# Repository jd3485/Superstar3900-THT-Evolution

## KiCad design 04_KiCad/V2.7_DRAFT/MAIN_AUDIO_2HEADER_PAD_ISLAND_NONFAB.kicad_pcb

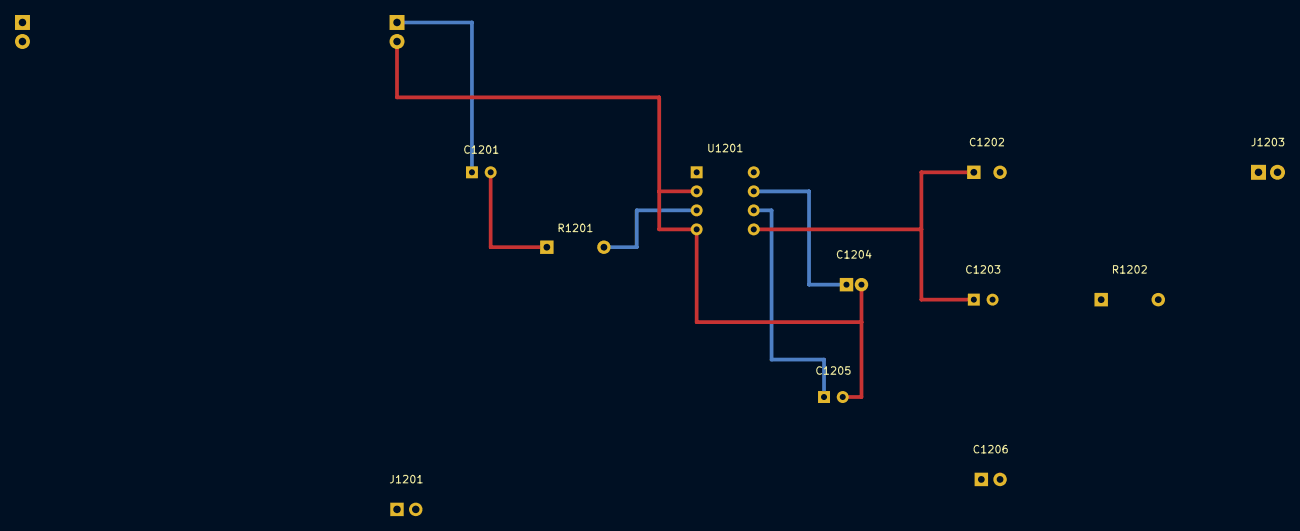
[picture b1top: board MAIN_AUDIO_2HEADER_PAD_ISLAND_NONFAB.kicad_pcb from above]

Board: 2 copper layers, 13 parts (0 on the bottom side), 9 nets.

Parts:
C1201: 100nF_50V_INPUT_UNQUALIFIED; C_Disc_D3.0mm_W1.6mm_P2.50mm
C1202: 220uF_16V_POS_TO_AMP_OUT_CANDIDATE_NONFAB; CP_Radial_D8.0mm_P3.50mm
C1203: 47nF_50V_ZOBEL_CANDIDATE_NONFAB; C_Disc_D3.0mm_W1.6mm_P2.50mm
C1204: 10uF_16V_BYPASS_CANDIDATE; CP_Radial_D5.0mm_P2.00mm
C1205: 100nF_25V_DECOUPLE_CANDIDATE; C_Disc_D3.0mm_W1.6mm_P2.50mm
C1206: 100uF_16V_BULK_CANDIDATE_NONFAB; CP_Radial_D6.3mm_P2.50mm
J1201: BENCH_6V_SOURCE_UNQUALIFIED_CANDIDATE_NONFAB; JST_XH_B2B-XH-A_1x02_P2.50mm_Vertical
J1202, J1502: NONFAB_MAIN_AUDIO_HEADER_PAD_ISLAND; PinHeader_1x02_P2.54mm_Vertical
J1203: SPK_OUT_CANDIDATE_NONFAB; PinHeader_1x02_P2.54mm_Vertical
R1201: 10k_0p25W_INPUT_UNQUALIFIED; R_Axial_DIN0207_L6.3mm_D2.5mm_P7.62mm_Horizontal
R1202: 10R_0p25W_ZOBEL_CANDIDATE_NONFAB; R_Axial_DIN0207_L6.3mm_D2.5mm_P7.62mm_Horizontal
U1201: LM386N-1/NOPB_CANDIDATE; DIP-8_W7.62mm

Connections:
AMP_IN: R1201.2, U1201.3
AMP_OUT: C1202.1, C1203.1, U1201.5
AUDIO_6V_LAB: C1205.1, C1206.1, J1201.1, U1201.6
AUDIO_IN: C1201.1, J1202.1
BYPASS: C1204.1, U1201.7
GND: C1204.2, C1205.2, C1206.2, J1201.2, J1202.2, J1203.2, R1202.2, U1201.2, U1201.4
PRE_IN: C1201.2, R1201.1
SPK_HOT: C1202.2, J1203.1
ZOBEL: C1203.2, R1202.1

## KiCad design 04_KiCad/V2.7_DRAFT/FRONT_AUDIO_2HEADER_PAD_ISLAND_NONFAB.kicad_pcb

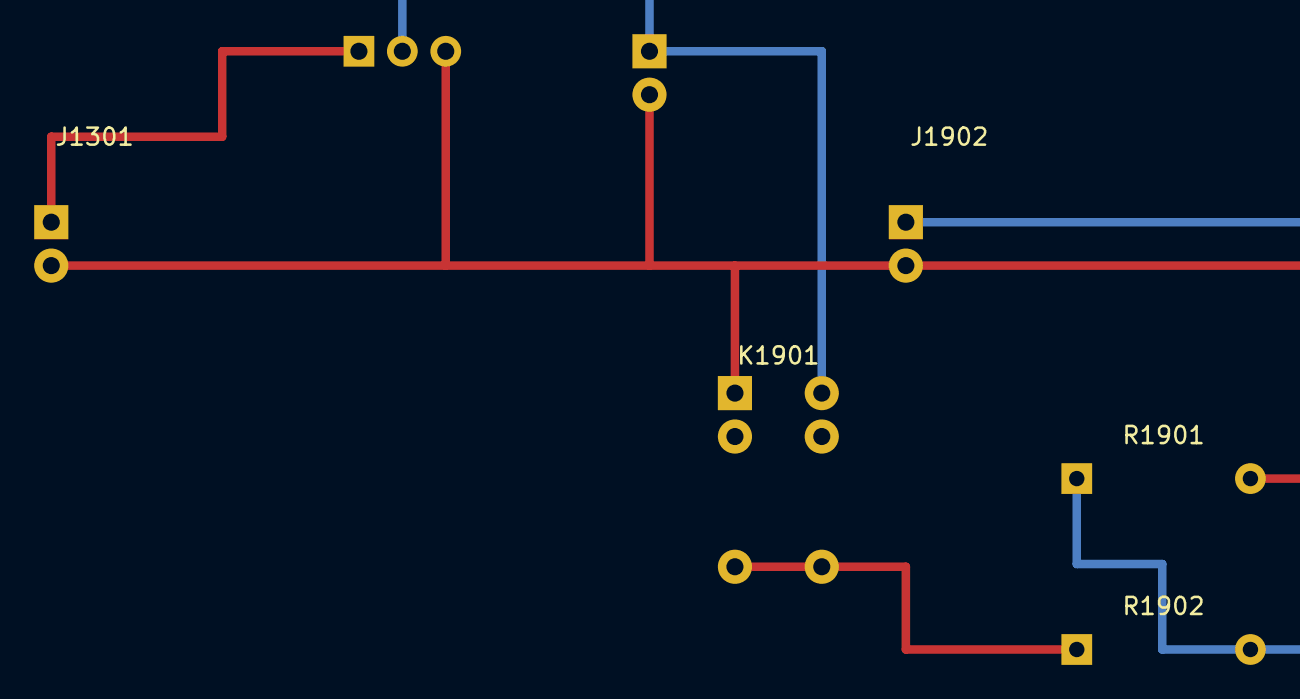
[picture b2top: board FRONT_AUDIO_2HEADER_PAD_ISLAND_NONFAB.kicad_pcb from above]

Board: 2 copper layers, 7 parts (0 on the bottom side), 5 nets.

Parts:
J1301, J1902: NONFAB_FRONT_AUDIO_HEADER_PAD_ISLAND; PinHeader_1x02_P2.54mm_Vertical
J1302: NONFAB_VOLUME_WIPER_HEADER; PinHeader_1x02_P2.54mm_Vertical
K1901: G5V1_DC5_SIXPIN_UNQUALIFIED; G5V-1_DC5_OEM_6PIN_CANDIDATE
R1901: 100k bleed, provisional; R_Axial_DIN0207_L6.3mm_D2.5mm_P10.16mm_Horizontal
R1902: 1k series, provisional; R_Axial_DIN0207_L6.3mm_D2.5mm_P10.16mm_Horizontal
RV1301: NONFAB_VOLUME_THT_CANDIDATE; Potentiometer_THT_3Pin_PROVISIONAL

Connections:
AF_GND: J1301.2, J1302.2, J1902.2, K1901.1, R1901.2, RV1301.3
AMP_INPUT_MUTED: J1902.1, R1901.1, R1902.2
DEMOD_AUDIO: J1301.1, RV1301.1
RELAY_COM_AUDIO: K1901.5, K1901.6, R1902.1
VOL_WIPER_TO_AMP: J1302.1, K1901.10, RV1301.2

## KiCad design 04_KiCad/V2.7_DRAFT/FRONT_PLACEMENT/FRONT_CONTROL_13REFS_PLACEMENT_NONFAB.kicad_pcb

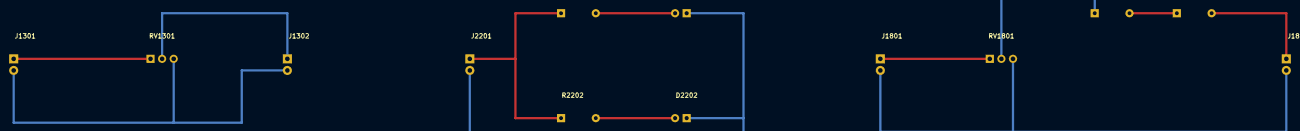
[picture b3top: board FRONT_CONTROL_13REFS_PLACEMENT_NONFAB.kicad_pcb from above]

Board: 2 copper layers, 13 parts (0 on the bottom side), 12 nets.

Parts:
D2201, D2202: NONFAB_LED_THT_PLACEMENT_ONLY; LED_D5.0mm
J1301, J1302, J1801, J1802, J2201: NONFAB_HEADER_THT_PLACEMENT_ONLY; PinHeader_1x02_P2.54mm_Vertical
R1801, R1802, R2201, R2202: NONFAB_RES_THT_PLACEMENT_ONLY; R_Axial_DIN0207_L6.3mm_D2.5mm_P7.62mm_Horizontal
RV1301, RV1801: NONFAB_POT_THT_PLACEMENT_ONLY; Potentiometer_THT_3Pin_PROVISIONAL

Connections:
AF_GND: J1301.2, J1302.2, RV1301.3
DEMOD_AUDIO: J1301.1, RV1301.1
ILLUM_5V_LAB: J2201.1, R2201.1, R2202.1
ILLUM_LED1_A: D2201.2, R2201.2
ILLUM_LED2_A: D2202.2, R2202.2
ILLUM_RETURN_LAB: D2201.1, D2202.1, J2201.2
METER_DRIVE_CANDIDATE: J1801.1, RV1801.1
METER_LIMIT_STAGE1: R1801.2, R1802.1
METER_POS_LIMITED: J1802.1, R1802.2
METER_RETURN: J1801.2, J1802.2, RV1801.3
METER_TRIM_OUTPUT: R1801.1, RV1801.2
VOL_WIPER_TO_AMP: J1302.1, RV1301.2

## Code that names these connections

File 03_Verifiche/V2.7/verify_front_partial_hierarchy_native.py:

#!/usr/bin/env python3
"""KiCad9 hierarchical FRONT integration pilot, five real THT sheets with four explicit inter-sheet nets.

Intended future FRONT parent but NOT an approved product schematic: existing
volume, LED, S-meter, relay contact and dual NPN coil driver sheets are included without making power,
return, cable or S-meter driver electrical interconnections. Fail on ERC violations
and accidental net merging across child pages.
"""
from pathlib import Path
import re
import subprocess
import tempfile

ROOT=Path(__file__).resolve().parents[2]
SCH=ROOT/"04_KiCad/V2.7_DRAFT/FRONT_CONTROL_PARTIAL_V2_7_DRAFT.kicad_sch"
CHILDREN=(
    ROOT/"04_KiCad/V2.7_DRAFT/FRONT_VOLUME/FRONT_VOLUME_THT_V2_7_DRAFT.kicad_sch",
    ROOT/"04_KiCad/V2.7_DRAFT/FRONT_ILLUM_BENCH/FRONT_ILLUM_BENCH_V2_7_DRAFT.kicad_sch",
    ROOT/"04_KiCad/V2.7_DRAFT/FRONT_SMETER/FRONT_SMETER_THT_V2_7_DRAFT.kicad_sch",
    ROOT/"04_KiCad/V2.7_DRAFT/FRONT_MUTE_NC_RELAY/FRONT_NC_MUTE_CONTACT_THT_V2_7_DRAFT.kicad_sch",
    ROOT/"04_KiCad/V2.7_DRAFT/FRONT_MUTE_COIL_DRIVER/FRONT_NC_MUTE_DUAL_ENABLE_COIL_DRIVER_V2_7_DRAFT.kicad_sch",
)
PARTITIONS={
    "DEMOD_AUDIO":{("J1301","1"),("RV1301","1")},
    "AF_GND":{("J1301","2"),("RV1301","3"),("J1302","2")},
    "VOL_WIPER_TO_AMP":{("RV1301","2"),("J1302","1")},
    "ILLUM_5V_LAB":{("J2201","1"),("R2201","1"),("R2202","1")},
    "ILLUM_RETURN_LAB":{("J2201","2"),("D2201","1"),("D2202","1")},
    "ILLUM_LED1_A":{("R2201","2"),("D2201","2")},
    "ILLUM_LED2_A":{("R2202","2"),("D2202","2")},
    "METER_DRIVE_CANDIDATE":{("J1801","1"),("RV1801","1")},
    "METER_TRIM_OUTPUT":{("RV1801","2"),("R1801","1")},
    "METER_LIMIT_STAGE1":{("R1801","2"),("R1802","1")},
    "METER_POS_LIMITED":{("R1802","2"),("J1802","1")},
    "METER_RETURN":{("J1801","2"),("RV1801","3"),("J1802","2")},
    "AMP_INPUT_MUTED":{("J1902","1"),("R1901","1"),("R1902","2")},
    "RELAY_COM_AUDIO":{("K1901","1"),("R1902","1")},
    "COIL_PLUS_LAB":{("K1901","4"),("J1903","1")},
    "COIL_MINUS_LAB":{("K1901","5"),("J1903","2")},
    "SERIES_MID":{("Q1911","3"),("Q1912","1"),("R1913","2")},
    "DRIVER_GND":{("Q1912","3"),("R1914","2"),("J1911","2"),("J1912","2"),("J1913","2"),("C1911","2"),("C1912","2")},
    "DRIVE1_BASE":{("Q1911","2"),("R1911","2"),("R1913","1")},
    "DRIVE2_BASE":{("Q1912","2"),("R1912","2"),("R1914","1")},
    "ENABLE_AUDIO_LAB":{("J1912","1"),("R1911","1")},
    "POWER_GOOD_LAB":{("J1913","1"),("R1912","1")},
}


def verify():
    sch=SCH.read_text(encoding="utf-8")
    assert sch.count("(sheet (at ")==5
    assert sch.count('(property "Sheetfile"')==5
    assert "FRONT_VOLUME/FRONT_VOLUME_THT_V2_7_DRAFT.kicad_sch" in sch
    assert "FRONT_ILLUM_BENCH/FRONT_ILLUM_BENCH_V2_7_DRAFT.kicad_sch" in sch
    assert "FRONT_SMETER/FRONT_SMETER_THT_V2_7_DRAFT.kicad_sch" in sch
    assert "FRONT_MUTE_NC_RELAY/FRONT_NC_MUTE_CONTACT_THT_V2_7_DRAFT.kicad_sch" in sch
    assert "FRONT_MUTE_COIL_DRIVER/FRONT_NC_MUTE_DUAL_ENABLE_COIL_DRIVER_V2_7_DRAFT.kicad_sch" in sch
    assert all(x.exists() for x in CHILDREN)
    project=SCH.with_suffix(".kicad_pro")
    symtab=SCH.parent/"sym-lib-table"
    fptab=SCH.parent/"fp-lib-table"
    assert project.is_file() and symtab.is_file() and fptab.is_file()
    sym=symtab.read_text(encoding="utf-8")
    fp=fptab.read_text(encoding="utf-8")
    for item in ("TH_FRONT", "TH_FRONT_ILLUM", "TH_SMETER", "TH_AUDIO", "TH_MUTE", "TH_COIL"):
        assert '(name "'+item+'")' in sym,item
    for item in ("TH_FRONT", "TH_FRONT_ILLUM_LAB"):
        assert '(name "'+item+'")' in fp,item
    assert sch.count("(wire (pts ")==10 and "(junction " not in sch
    assert sch.count('(pin "VOL_WIPER_TO_AMP" passive')==2
    assert sch.count('(pin "AF_GND" passive')==2
    assert sch.count('(pin "COIL_PLUS_LAB" passive')==2
    assert sch.count('(pin "COIL_MINUS_LAB" passive')==2
    assert sch.count('(pin "METER_DRIVE_CANDIDATE" passive')==1
    assert sch.count('(pin "METER_RETURN" passive')==1
    assert sch.count('(label "METER_DRIVE_CANDIDATE"')==1
    assert sch.count('(label "METER_RETURN"')==1
    assert '<escape>' not in sch
    assert "NO FAB / NO TX" in sch
    with tempfile.TemporaryDirectory(prefix="tht_front_partial_hierarchy_") as temp:
        d=Path(temp)
        erc=d/"erc.rpt"
        cp=subprocess.run(["kicad-cli","sch","erc","--exit-code-violations",
                           "-o",str(erc),str(SCH)],cwd=ROOT,capture_output=True,text=True,timeout=120)
        print("FRONT_PARTIAL_HIERARCHY_ERC_STDOUT",cp.stdout,cp.stderr,flush=True)
        if erc.exists():
            print("FRONT_PARTIAL_HIERARCHY_ERC_REPORT",erc.read_text(encoding="utf-8"),flush=True)
        cp.check_returncode()
        net=d/"front.net"
        cp=subprocess.run(["kicad-cli","sch","export","netlist","-o",str(net),str(SCH)],
            cwd=ROOT,capture_output=True,text=True,timeout=120)
        print("FRONT_PARTIAL_HIERARCHY_EXPORT",cp.stdout,cp.stderr,flush=True)
        cp.check_returncode()
        raw=net.read_text(encoding="utf-8")
    assert "(nets" in raw
    # Hierarchical local net names are sheet-prefixed; ensure no new
    # unintentional tie between audio/AGC and LED switching return.
    blocks=raw.rsplit("(nets",1)[1]
    headers=list(re.finditer(
        r'\(net\s+\(code\s+"?\d+"?\)\s+\(name\s+"([^"]+)"\)',blocks))
    found={}
    for i,h in enumerate(headers):
        block=blocks[h.end():headers[i+1].start() if i+1<len(headers) else len(blocks)]
        members=set(re.findall(
            r'\(node\s+\(ref\s+"([^"]+)"\)\s+\(pin\s+"([^"]+)"\)',block))
        label=h.group(1).rsplit("/",1)[-1]
        found.setdefault(label,[]).append(members)
    assert set(found)==set(PARTITIONS),(found.keys(),PARTITIONS.keys())
    joined={
        "AF_GND":{("J1301","2"),("RV1301","3"),("J1302","2"),
                  ("K1901","2"),("J1901","2"),("J1902","2"),("R1901","2")},
        "VOL_WIPER_TO_AMP":{("RV1301","2"),("J1302","1"),("K1901","3"),("J1901","1")},
        "COIL_PLUS_LAB":{("K1901","4"),("J1903","1"),("J1911","1"),("D1911","1"),("J1914","1"),("C1911","1"),("C1912","1")},
        "COIL_MINUS_LAB":{("K1901","5"),("J1903","2"),("J1914","2"),("D1911","2"),("Q1911","1")},
    }
    for name,expected in PARTITIONS.items():
        candidates=found[name]
        if name in joined:
            assert candidates==[joined[name]],(name,candidates,joined[name])
            continue
        assert candidates==[expected],(name,candidates,expected)
    all_nets=[pins for group in found.values() for pins in group]
    assert len(all_nets)==22,len(all_nets)
    assert len(set().union(*all_nets))==sum(map(len,all_nets))==71
    assert all(len(found[name])==1 for name in joined)
    assert found["COIL_PLUS_LAB"][0].isdisjoint(found["COIL_MINUS_LAB"][0])
    assert found["METER_DRIVE_CANDIDATE"][0].isdisjoint(found["METER_RETURN"][0])
    assert found["METER_RETURN"][0].isdisjoint(found["AF_GND"][0])
    assert found["METER_RETURN"][0].isdisjoint(found["DRIVER_GND"][0])
    assert found["METER_RETURN"][0].isdisjoint(found["ILLUM_RETURN_LAB"][0])
    assert found["DRIVER_GND"][0].isdisjoint(found["AF_GND"][0])
    assert found["ILLUM_RETURN_LAB"][0].isdisjoint(found["DRIVER_GND"][0])
    print("PASS_KICAD9_FRONT_HIERARCHY_5SHEETS_32REFS_22NETS_71PINS_4REAL_AUDIO_COIL_JOINS_ERC0_NONFAB",{
        "child_sheets":5,
        "THT_components":32,
        "hierarchical_nets":22,
        "actual_volume_to_mute_signal_and_AF_GND_connections":2,
        "actual_coil_plus_minus_connections":2,
        "pin_endpoints":71,
        "relay_oem_qualified":False,
        "relay_coil_interconnected_in_parent":True,
        "relay_coil_qualified_for_product":False,
        "MAIN_FRONT_harness_qualified":False,
        "S_meter_passive_candidate_sheet_included":True,
        "S_meter_two_native_hierarchical_ports_present":True,
        "S_meter_return_AF_GND_joined":False,
        "S_meter_driver_FSD_coil_qualified":False,
        "hardware_production_PCB_exists":False,
        "NO_FAB_NO_TX":True,
    },flush=True)


if __name__=="__main__":
    verify()

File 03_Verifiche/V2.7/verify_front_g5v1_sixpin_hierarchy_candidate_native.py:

#!/usr/bin/env python3
"""KiCad9 native ERC/netlist contrast: five-sheet FRONT abstract vs 6-pin OEM candidate.
No product relay qualification, populated PCB or board DRC.
"""
from pathlib import Path
import tempfile
import subprocess
import sys

ROOT=Path(__file__).resolve().parents[2]
sys.path.insert(0,str(Path(__file__).resolve().parent))
from verify_interboard_audio_contract_native import exported_nets
from verify_front_partial_hierarchy_native import SCH as ABSTRACT
from verify_front_g5v1_six_terminal_oem_pin_map_native import OEM_TO_EXISTING_NET

CAND=ROOT/"04_KiCad/V2.7_DRAFT/FRONT_CONTROL_PARTIAL_G5V1_SIXPIN_CANDIDATE.kicad_sch"
OLD_RELAY="FRONT_MUTE_NC_RELAY/FRONT_NC_MUTE_CONTACT_THT_V2_7_DRAFT.kicad_sch"
NEW_RELAY="FRONT_MUTE_NC_RELAY/FRONT_G5V1_SIXPIN_POSTMUTE_HIERARCHICAL_CANDIDATE.kicad_sch"

def pinmap(nets):
    result={}
    for name, members in nets.items():
        for member in members:
            assert member not in result,(member,name,result[member])
            result[member]=name.rsplit("/",1)[-1]
    return result

def main():
    assert CAND.with_suffix(".kicad_pro").is_file()
    old_text=ABSTRACT.read_text(encoding="utf8")
    text=CAND.read_text(encoding="utf8")
    assert OLD_RELAY in old_text
    assert OLD_RELAY not in text
    assert text.count(NEW_RELAY)==1
    assert text.count('(pin "AMP_INPUT_MUTED" passive')==1
    assert text.count('(pin "AF_GND" passive')==3
    assert '(xy 205.74 237.49) (xy 217.17 237.49)' in text
    assert '(xy 205.74 242.57) (xy 217.17 242.57)' in text
    original_relay=ROOT/"04_KiCad/V2.7_DRAFT/FRONT_MUTE_NC_RELAY/FRONT_G5V1_SIXPIN_ISOLATED_NATIVE_CANDIDATE.kicad_sch"
    routed_relay=ROOT/"04_KiCad/V2.7_DRAFT"/NEW_RELAY
    assert original_relay.is_file() and routed_relay.is_file()
    original_text=original_relay.read_text(encoding="utf8")
    routed_text=routed_relay.read_text(encoding="utf8")
    assert routed_text.count('(hierarchical_label "AMP_INPUT_MUTED"')==1
    assert routed_text.count('(hierarchical_label "AF_GND"')==2
    assert '(hierarchical_label "AMP_INPUT_MUTED"' not in original_text
    # The actual J1301/1 demod input must be exported to the FRONT parent,
    # while the original standalone volume benchmark stays unchanged.
    child=ROOT/"04_KiCad/V2.7_DRAFT/FRONT_VOLUME/FRONT_VOLUME_THT_V2_7_DRAFT_FRONT_HIERARCHICAL_CANDIDATE.kicad_sch"
    standalone=ROOT/"04_KiCad/V2.7_DRAFT/FRONT_VOLUME/FRONT_VOLUME_THT_V2_7_DRAFT.kicad_sch"
    assert standalone.is_file() and child.is_file()
    assert "FRONT_VOLUME/FRONT_VOLUME_THT_V2_7_DRAFT_FRONT_HIERARCHICAL_CANDIDATE.kicad_sch" in text
    assert text.count('(pin "DEMOD_AUDIO" passive')==1
    assert text.count('(label "DEMOD_AUDIO" (at 165.1 111.76 0)')==1
    assert "(xy 142.24 111.76) (xy 165.1 111.76)" in text
    assert child.read_text(encoding="utf8").count('(hierarchical_label "DEMOD_AUDIO"')==1
    assert '(hierarchical_label "DEMOD_AUDIO"' not in standalone.read_text(encoding="utf8")
    assert "NO FAB / NO TX" in text
    assert text.count("(sheet (at ")==5
    assert text.count('(pin "COIL_PLUS_LAB" passive')==2
    assert text.count('(pin "COIL_MINUS_LAB" passive')==2
    with tempfile.TemporaryDirectory(prefix="front_6pin_hierarchy_") as td:
        d=Path(td)
        for sch,short in ((ABSTRACT,"abstract"),(CAND,"sixpin")):
            report=d/(short+".erc")
            run=subprocess.run(["kicad-cli","sch","erc","--exit-code-violations",
                                "-o",str(report),str(sch)],cwd=ROOT,
                                capture_output=True,text=True,timeout=120)
            if report.exists():print(short+"_ERC",report.read_text(encoding="utf8"),flush=True)
            print(short+"_ERC_RETURN",run.returncode,run.stdout,run.stderr,flush=True)
            run.check_returncode()
        old=exported_nets(ABSTRACT,d/"old.net")
        new=exported_nets(CAND,d/"candidate.net")
    om=pinmap(old); nm=pinmap(new)
    expected={("K1901",pin):name for pin,name in OEM_TO_EXISTING_NET.items()}
    candidate_relay={key:value for key,value in nm.items() if key[0]=="K1901"}
    assert candidate_relay==expected,(candidate_relay,expected)
    assert {k:v for k,v in om.items() if k[0]=="K1901"}=={
        ("K1901","1"):"RELAY_COM_AUDIO",
        ("K1901","2"):"AF_GND",
        ("K1901","3"):"VOL_WIPER_TO_AMP",
        ("K1901","4"):"COIL_PLUS_LAB",
        ("K1901","5"):"COIL_MINUS_LAB"}
    unaffected_old={k:v for k,v in om.items() if k[0]!="K1901"}
    unaffected_new={k:v for k,v in nm.items() if k[0]!="K1901"}
    assert unaffected_old==unaffected_new,(
        "non-relay endpoints changed",
        sorted(set(unaffected_old.items())-set(unaffected_new.items())),
        sorted(set(unaffected_new.items())-set(unaffected_old.items())))
    assert len(nm)==len(om)+1,(len(nm),len(om))
    assert len(old)==len(new)==22,(len(old),len(new))
    assert nm[("K1901","5")]=="RELAY_COM_AUDIO"
    assert nm[("K1901","6")]=="RELAY_COM_AUDIO"
    # Neither preexisting AF/driver isolation nor the audio-mute boundary may collapse.
    assert nm[("J1902","1")]=="AMP_INPUT_MUTED"
    assert nm[("J1302","1")]=="VOL_WIPER_TO_AMP"
    for left,right in (("AF_GND","DRIVER_GND"),("COIL_PLUS_LAB","COIL_MINUS_LAB"),
                       ("METER_RETURN","AF_GND"),("ILLUM_RETURN_LAB","AF_GND"),
                       ("RELAY_COM_AUDIO","AMP_INPUT_MUTED")):
        assert any(net.rsplit("/",1)[-1]==left for net in new),left
        assert any(net.rsplit("/",1)[-1]==right for net in new),right
        assert left!=right
    print("PASS_KICAD9_FRONT_5SHEETS_G5V1_SIX_PHYSICAL_PINS_72_ENDPOINTS_22_NETS_ERC0_CANDIDATE",{
        "original_endpoint_count":len(om),
        "candidate_endpoint_count":len(nm),
        "native_net_count":len(new),
        "all_other_component_pin_to_net_unchanged":True,
        "candidate_relay_pins":candidate_relay,
        "PCB_DRC_performed":False,
        "OEM_coil_contact_hardware_qualified":False,
        "NO_FAB_NO_TX_NO_BATTERY_NO_VEHICLE":True},flush=True)

if __name__=="__main__":
    main()
